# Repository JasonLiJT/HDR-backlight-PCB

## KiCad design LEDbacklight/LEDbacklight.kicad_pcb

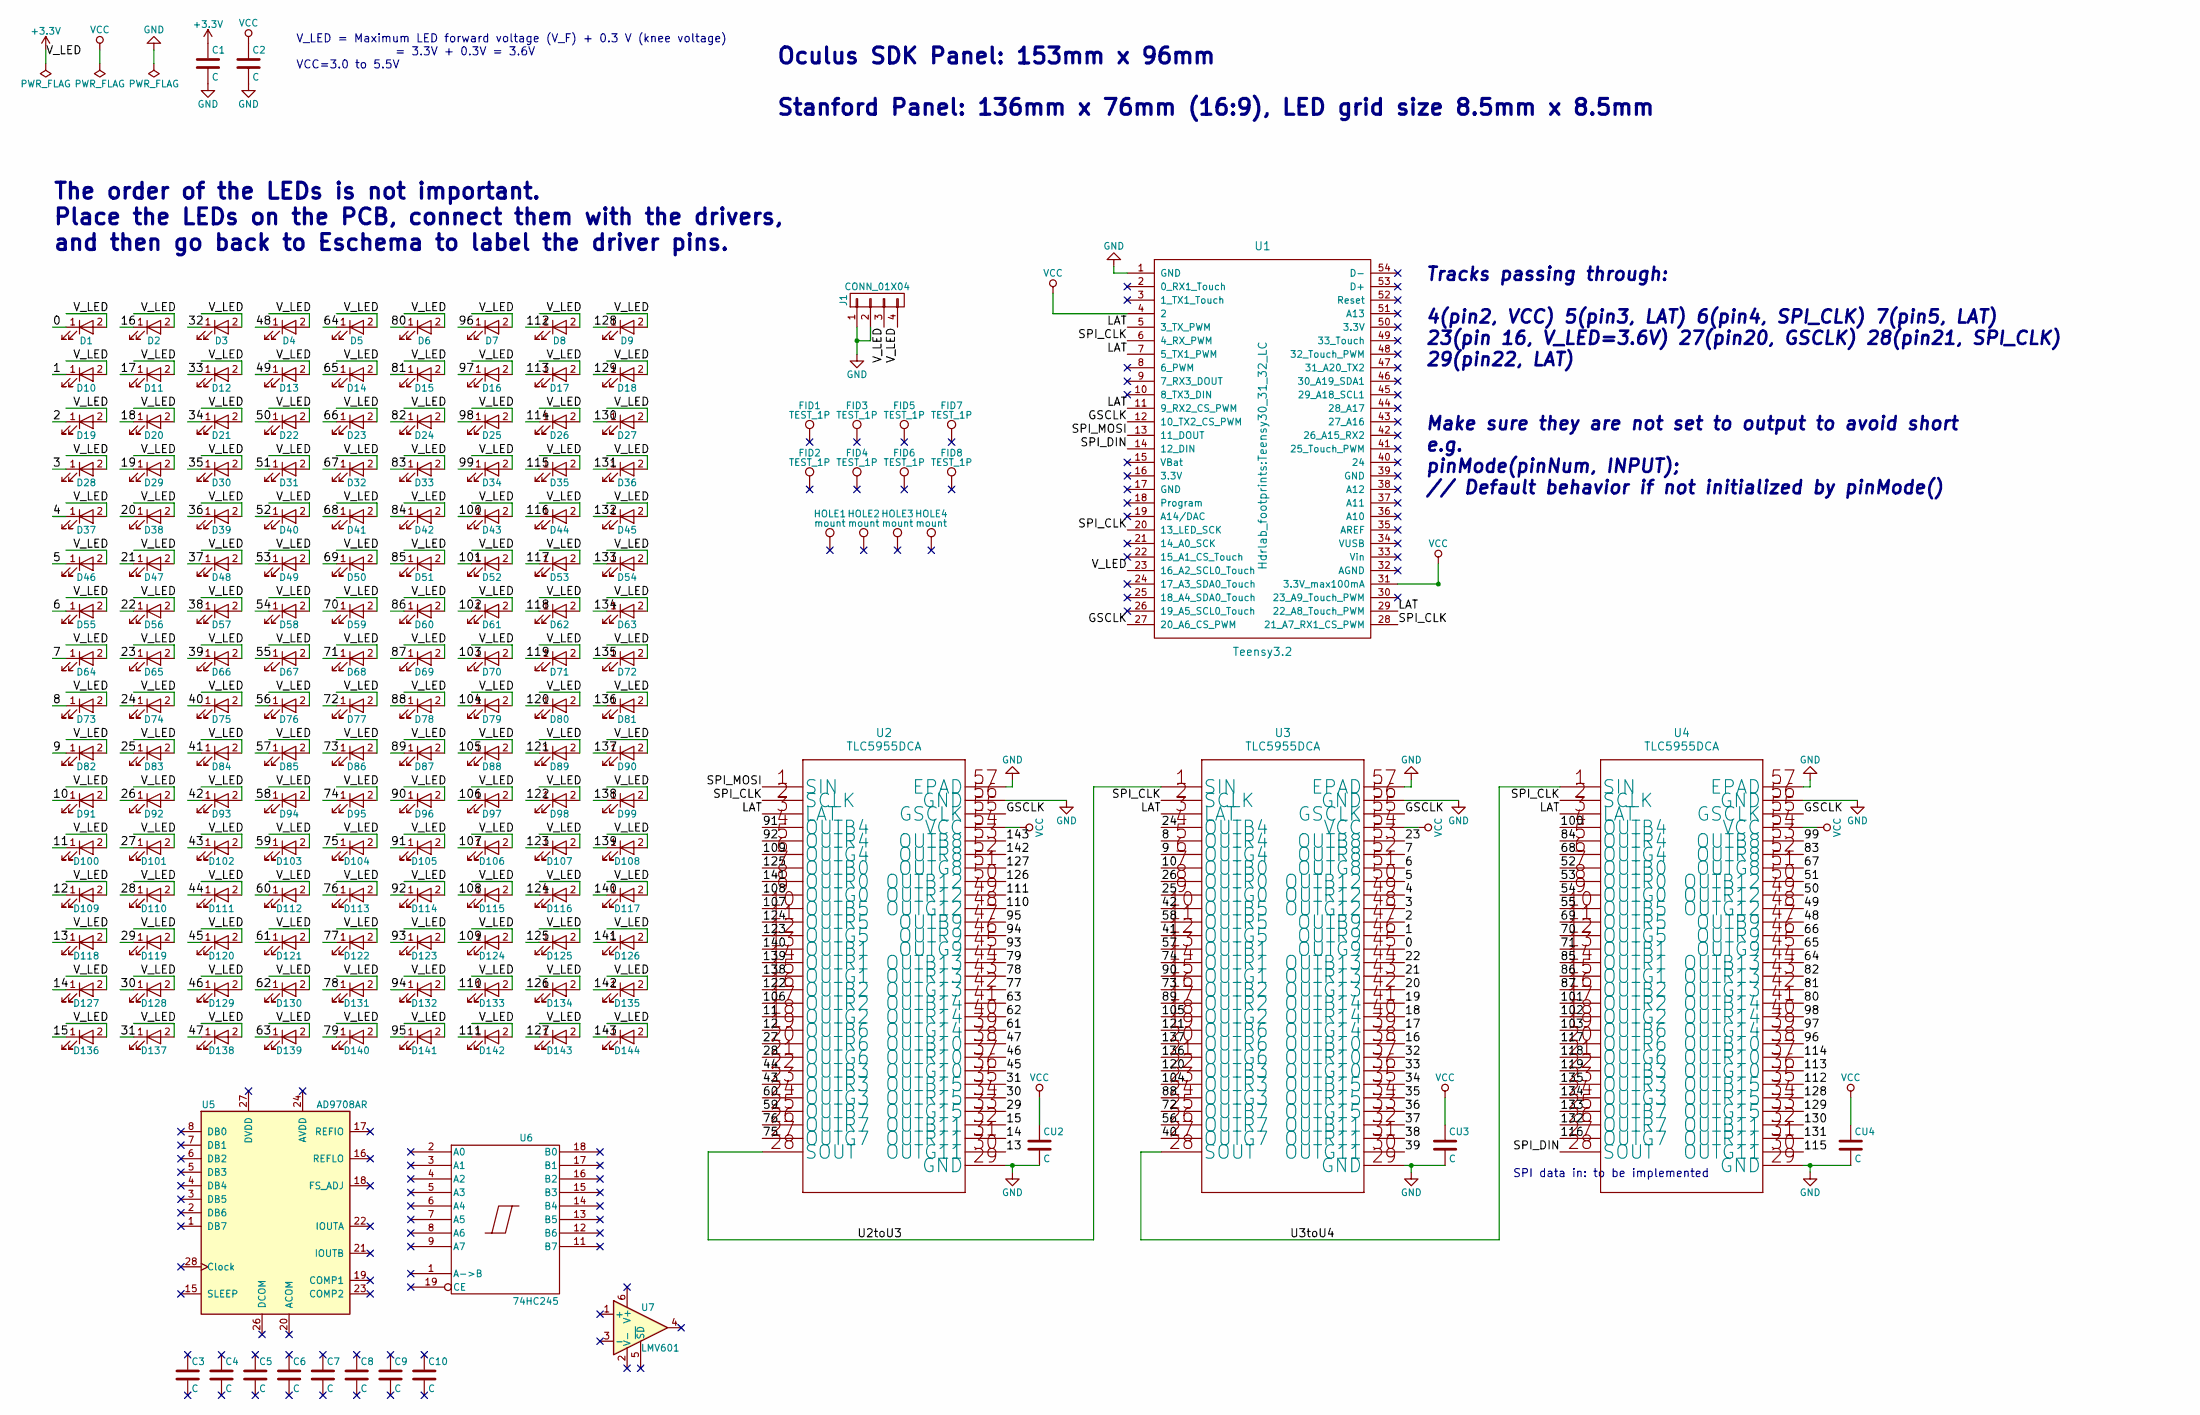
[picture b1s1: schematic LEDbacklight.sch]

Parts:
C1, C2, C3, C4, C5, C6, C7, C8, C9, C10: C; C_0603_HandSoldering
CU2, CU3, CU4: C; C_0603_HandSoldering
D1, D2, D3, D4, D5, D6, D7, D8, D9, D10, D11, D12, D13, D14, D15, D16, D17, D18, D19, D20, D21, D22, D23, D24, D25, D26, D27, D28, D29, D30, D31, D32, D33, D34, D35, D36, D37, D38, D39, D40, D41, D42, D43, D44, D45, D46, D47, D48, D49, D50, D51, D52, D53, D54, D55, D56, D57, D58, D59, D60, D61, D62, D63, D64, D65, D66, D67, D68, D69, D70, D71, D72, D73, D74, D75, D76, D77, D78, D79, D80, D81, D82, D83, D84, D85, D86, D87, D88, D89, D90, D91, D92, D93, D94, D95, D96, D97, D98, D99, D100, D101, D102, D103, D104, D105, D106, D107, D108, D109, D110, D111, D112, D113, D114, D115, D116, D117, D118, D119, D120, D121, D122, D123, D124, D125, D126, D127, D128, D129, D130, D131, D132, D133, D134, D135, D136, D137, D138, D139, D140, D141, D142, D143, D144: LED; LED_6500K
FID1, FID2, FID3, FID4: TEST_1P; Fiducial_1mm_Dia_2.54mm_Outer_CopperTop
FID5, FID6, FID7, FID8: TEST_1P; Fiducial_1mm_Dia_2.54mm_Outer_CopperBottom
HOLE1, HOLE2, HOLE3, HOLE4: mount; MountingHole_2.7mm_M2.5
J1: CONN_01X04; Molex_KK-6410-04_04x2.54mm_Straight
U1: Teensy3.2; Teensy30_31_32_LC
U2, U3, U4: TLC5955DCA
U5: AD9708AR; ETSSOP-20-1EP_4.4x6.5mm_Pitch0.65mm
U6: 74HC245; SSOP-20
U7: LMV601; SOT-23-6_Handsoldering

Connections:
+3V3: C1.1, D1.2 (A), D2.2 (A), D3.2 (A), D4.2 (A), D5.2 (A), D6.2 (A), D7.2 (A), D8.2 (A), D9.2 (A), D10.2 (A), D11.2 (A), D12.2 (A), D13.2 (A), D14.2 (A), D15.2 (A), D16.2 (A), D17.2 (A), D18.2 (A), D19.2 (A), D20.2 (A), D21.2 (A), D22.2 (A), D23.2 (A), D24.2 (A), D25.2 (A), D26.2 (A), D27.2 (A), D28.2 (A), D29.2 (A), D30.2 (A), D31.2 (A), D32.2 (A), D33.2 (A), D34.2 (A), D35.2 (A), D36.2 (A), D37.2 (A), D38.2 (A), D39.2 (A), D40.2 (A), D41.2 (A), D42.2 (A), D43.2 (A), D44.2 (A), D45.2 (A), D46.2 (A), D47.2 (A), D48.2 (A), D49.2 (A), D50.2 (A), D51.2 (A), D52.2 (A), D53.2 (A), D54.2 (A), D55.2 (A), D56.2 (A), D57.2 (A), D58.2 (A), D59.2 (A), D60.2 (A), D61.2 (A), D62.2 (A), D63.2 (A), D64.2 (A), D65.2 (A), D66.2 (A), D67.2 (A), D68.2 (A), D69.2 (A), D70.2 (A), D71.2 (A), D72.2 (A), D73.2 (A), D74.2 (A), D75.2 (A), D76.2 (A), D77.2 (A), D78.2 (A), D79.2 (A), D80.2 (A), D81.2 (A), D82.2 (A), D83.2 (A), D84.2 (A), D85.2 (A), D86.2 (A), D87.2 (A), D88.2 (A), D89.2 (A), D90.2 (A), D91.2 (A), D92.2 (A), D93.2 (A), D94.2 (A), D95.2 (A), D96.2 (A), D97.2 (A), D98.2 (A), D99.2 (A), D100.2 (A), D101.2 (A), D102.2 (A), D103.2 (A), D104.2 (A), D105.2 (A), D106.2 (A), D107.2 (A), D108.2 (A), D109.2 (A), D110.2 (A), D111.2 (A), D112.2 (A), D113.2 (A), D114.2 (A), D115.2 (A), D116.2 (A), D117.2 (A), D118.2 (A), D119.2 (A), D120.2 (A), D121.2 (A), D122.2 (A), D123.2 (A), D124.2 (A), D125.2 (A), D126.2 (A), D127.2 (A), D128.2 (A), D129.2 (A), D130.2 (A), D131.2 (A), D132.2 (A), D133.2 (A), D134.2 (A), D135.2 (A), D136.2 (A), D137.2 (A), D138.2 (A), D139.2 (A), D140.2 (A), D141.2 (A), D142.2 (A), D143.2 (A), D144.2 (A), J1.3, J1.4, U1.23 (16_A2_SCL0_Touch)
/0: D1.1 (K), U3.45 (OUTG9)
/1: D10.1 (K), U3.46 (OUTR9)
/2: D19.1 (K), U3.47 (OUTB9)
/3: D28.1 (K), U3.48 (OUTG12)
/4: D37.1 (K), U3.49 (OUTR12)
/5: D46.1 (K), U3.50 (OUTB12)
/6: D55.1 (K), U3.51 (OUTG8)
/7: D64.1 (K), U3.52 (OUTR8)
/8: D73.1 (K), U3.5 (OUTR4)
/9: D82.1 (K), U3.6 (OUTG4)
/10: D91.1 (K), U3.7 (OUTB0)
/11: D100.1 (K), U2.18 (OUTG2)
/12: D109.1 (K), U2.19 (OUTB6)
/13: D118.1 (K), U2.30 (OUTG11)
/14: D127.1 (K), U2.31 (OUTR11)
/15: D136.1 (K), U2.32 (OUTB11)
/16: D2.1 (K), U3.38 (OUTB10)
/17: D11.1 (K), U3.39 (OUTG14)
/18: D20.1 (K), U3.40 (OUTR14)
/19: D29.1 (K), U3.41 (OUTB14)
/20: D38.1 (K), U3.42 (OUTG13)
/21: D47.1 (K), U3.43 (OUTR13)
/22: D56.1 (K), U3.44 (OUTB13)
/23: D65.1 (K), U3.53 (OUTB8)
/24: D74.1 (K), U3.4 (OUTB4)
/25: D83.1 (K), U3.9 (OUTG0)
/26: D92.1 (K), U3.8 (OUTR0)
/27: D101.1 (K), U2.20 (OUTR6)
/28: D110.1 (K), U2.21 (OUTG6)
/29: D119.1 (K), U2.33 (OUTG15)
/30: D128.1 (K), U2.34 (OUTR15)
/31: D137.1 (K), U2.35 (OUTB15)
/32: D3.1 (K), U3.37 (OUTR10)
/33: D12.1 (K), U3.36 (OUTG10)
/34: D21.1 (K), U3.35 (OUTB15)
/35: D30.1 (K), U3.34 (OUTR15)
/36: D39.1 (K), U3.33 (OUTG15)
/37: D48.1 (K), U3.32 (OUTB11)
/38: D57.1 (K), U3.31 (OUTR11)
/39: D66.1 (K), U3.30 (OUTG11)
/40: D75.1 (K), U3.27 (OUTG7)
/41: D84.1 (K), U3.12 (OUTG5)
/42: D93.1 (K), U3.10 (OUTB5)
/43: D102.1 (K), U2.23 (OUTR3)
/44: D111.1 (K), U2.22 (OUTB3)
/45: D120.1 (K), U2.36 (OUTG10)
/46: D129.1 (K), U2.37 (OUTR10)
/47: D138.1 (K), U2.38 (OUTB10)
/48: D4.1 (K), U4.47 (OUTB9)
/49: D13.1 (K), U4.48 (OUTG12)
/50: D22.1 (K), U4.49 (OUTR12)
/51: D31.1 (K), U4.50 (OUTB12)
/52: D40.1 (K), U4.7 (OUTB0)
/53: D49.1 (K), U4.8 (OUTR0)
/54: D58.1 (K), U4.9 (OUTG0)
/55: D67.1 (K), U4.10 (OUTB5)
/56: D76.1 (K), U3.26 (OUTR7)
/57: D85.1 (K), U3.13 (OUTB1)
/58: D94.1 (K), U3.11 (OUTR5)
/59: D103.1 (K), U2.25 (OUTB7)
/60: D112.1 (K), U2.24 (OUTG3)
/61: D121.1 (K), U2.39 (OUTG14)
/62: D130.1 (K), U2.40 (OUTR14)
/63: D139.1 (K), U2.41 (OUTB14)
/64: D5.1 (K), U4.44 (OUTB13)
/65: D14.1 (K), U4.45 (OUTG9)
/66: D23.1 (K), U4.46 (OUTR9)
/67: D32.1 (K), U4.51 (OUTG8)
/68: D41.1 (K), U4.6 (OUTG4)
/69: D50.1 (K), U4.11 (OUTR5)
/70: D59.1 (K), U4.12 (OUTG5)
/71: D68.1 (K), U4.13 (OUTB1)
/72: D77.1 (K), U3.25 (OUTB7)
/73: D86.1 (K), U3.16 (OUTB2)
/74: D95.1 (K), U3.14 (OUTR1)
/75: D104.1 (K), U2.27 (OUTG7)
/76: D113.1 (K), U2.26 (OUTR7)
/77: D122.1 (K), U2.42 (OUTG13)
/78: D131.1 (K), U2.43 (OUTR13)
/79: D140.1 (K), U2.44 (OUTB13)
/80: D6.1 (K), U4.41 (OUTB14)
/81: D15.1 (K), U4.42 (OUTG13)
/82: D24.1 (K), U4.43 (OUTR13)
/83: D33.1 (K), U4.52 (OUTR8)
/84: D42.1 (K), U4.5 (OUTR4)
/85: D51.1 (K), U4.14 (OUTR1)
/86: D60.1 (K), U4.15 (OUTG1)
/87: D69.1 (K), U4.16 (OUTB2)
/88: D78.1 (K), U3.24 (OUTG3)
/89: D87.1 (K), U3.17 (OUTR2)
/90: D96.1 (K), U3.15 (OUTG1)
/91: D105.1 (K), U2.4 (OUTB4)
/92: D114.1 (K), U2.5 (OUTR4)
/93: D123.1 (K), U2.45 (OUTG9)
/94: D132.1 (K), U2.46 (OUTR9)
/95: D141.1 (K), U2.47 (OUTB9)
/96: D7.1 (K), U4.38 (OUTB10)
/97: D16.1 (K), U4.39 (OUTG14)
/98: D25.1 (K), U4.40 (OUTR14)
/99: D34.1 (K), U4.53 (OUTB8)
/100: D43.1 (K), U4.4 (OUTB4)
/101: D52.1 (K), U4.17 (OUTR2)
/102: D61.1 (K), U4.18 (OUTG2)
/103: D70.1 (K), U4.19 (OUTB6)
/104: D79.1 (K), U3.23 (OUTR3)
/105: D88.1 (K), U3.18 (OUTG2)
/106: D97.1 (K), U2.17 (OUTR2)
/107: D106.1 (K), U2.10 (OUTB5)
/108: D115.1 (K), U2.9 (OUTG0)
/109: D124.1 (K), U2.6 (OUTG4)
/110: D133.1 (K), U2.48 (OUTG12)
/111: D142.1 (K), U2.49 (OUTR12)
/112: D8.1 (K), U4.35 (OUTB15)
/113: D17.1 (K), U4.36 (OUTG10)
/114: D26.1 (K), U4.37 (OUTR10)
/115: D35.1 (K), U4.30 (OUTG11)
/116: D44.1 (K), U4.27 (OUTG7)
/117: D53.1 (K), U4.20 (OUTR6)
/118: D62.1 (K), U4.21 (OUTG6)
/119: D71.1 (K), U4.22 (OUTB3)
/120: D80.1 (K), U3.22 (OUTB3)
/121: D89.1 (K), U3.19 (OUTB6)
/122: D98.1 (K), U2.16 (OUTB2)
/123: D107.1 (K), U2.12 (OUTG5)
/124: D116.1 (K), U2.11 (OUTR5)
/125: D125.1 (K), U2.7 (OUTB0)
/126: D134.1 (K), U2.50 (OUTB12)
/127: D143.1 (K), U2.51 (OUTG8)
/128: D9.1 (K), U4.34 (OUTR15)
/129: D18.1 (K), U4.33 (OUTG15)
/130: D27.1 (K), U4.32 (OUTB11)
/131: D36.1 (K), U4.31 (OUTR11)
/132: D45.1 (K), U4.26 (OUTR7)
/133: D54.1 (K), U4.25 (OUTB7)
/134: D63.1 (K), U4.24 (OUTG3)
/135: D72.1 (K), U4.23 (OUTR3)
/136: D81.1 (K), U3.21 (OUTG6)
/137: D90.1 (K), U3.20 (OUTR6)
/138: D99.1 (K), U2.15 (OUTG1)
/139: D108.1 (K), U2.14 (OUTR1)
/140: D117.1 (K), U2.13 (OUTB1)
/141: D126.1 (K), U2.8 (OUTR0)
/142: D135.1 (K), U2.52 (OUTR8)
/143: D144.1 (K), U2.53 (OUTB8)
/GSCLK: U1.12 (10_TX2_CS_PWM), U1.27 (20_A6_CS_PWM), U2.55 (GSCLK), U3.55 (GSCLK), U4.55 (GSCLK)
/LAT: U1.5 (3_TX_PWM), U1.7 (5_TX1_PWM), U1.11 (9_RX2_CS_PWM), U1.29 (22_A8_Touch_PWM), U2.3 (LAT), U3.3 (LAT), U4.3 (LAT)
/SPI_CLK: U1.6 (4_RX_PWM), U1.20 (13_LED_SCK), U1.28 (21_A7_RX1_CS_PWM), U2.2 (SCLK), U3.2 (SCLK), U4.2 (SCLK)
/SPI_DIN: U1.14 (12_DIN), U4.28 (SOUT)
/SPI_MOSI: U1.13 (11_DOUT), U2.1 (SIN)
/U2toU3: U2.28 (SOUT), U3.1 (SIN)
/U3toU4: U3.28 (SOUT), U4.1 (SIN)
GND: C1.2, C2.2, CU2.2, CU3.2, CU4.2, J1.1, J1.2, U1.1 (GND), U2.29 (GND), U2.56 (GND), U2.57 (EPAD), U3.29 (GND), U3.56 (GND), U3.57 (EPAD), U4.29 (GND), U4.56 (GND), U4.57 (EPAD), U6.10 (GND)
VCC: C2.1, CU2.1, CU3.1, CU4.1, U1.4 (2), U1.31 (3.3V_max100mA), U2.54 (VCC), U3.54 (VCC), U4.54 (VCC), U6.20 (VCC)

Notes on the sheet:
V_LED = Maximum LED forward voltage (V_F) + 0.3 V (knee voltage) = 3.3V + 0.3V = 3.6V VCC=3.0 to 5.5V
Oculus SDK Panel: 153mm x 96mm Stanford Panel: 136mm x 76mm (16:9), LED grid size 8.5mm x 8.5mm
The order of the LEDs is not important. Place the LEDs on the PCB, connect them with the drivers, and then go back to Eschema to label the driver pins.
SPI data in: to be implemented
Tracks passing through: 4(pin2, VCC) 5(pin3, LAT) 6(pin4, SPI_CLK) 7(pin5, LAT) 23(pin 16, V_LED=3.6V) 27(pin20, GSCLK) 28(pin21, SPI_CLK) 29(pin22, LAT) Make sure they are not set to output to avoid short e.g. pinMode(pinNum, INPUT); // Default behavior if not initialized by pinMode()

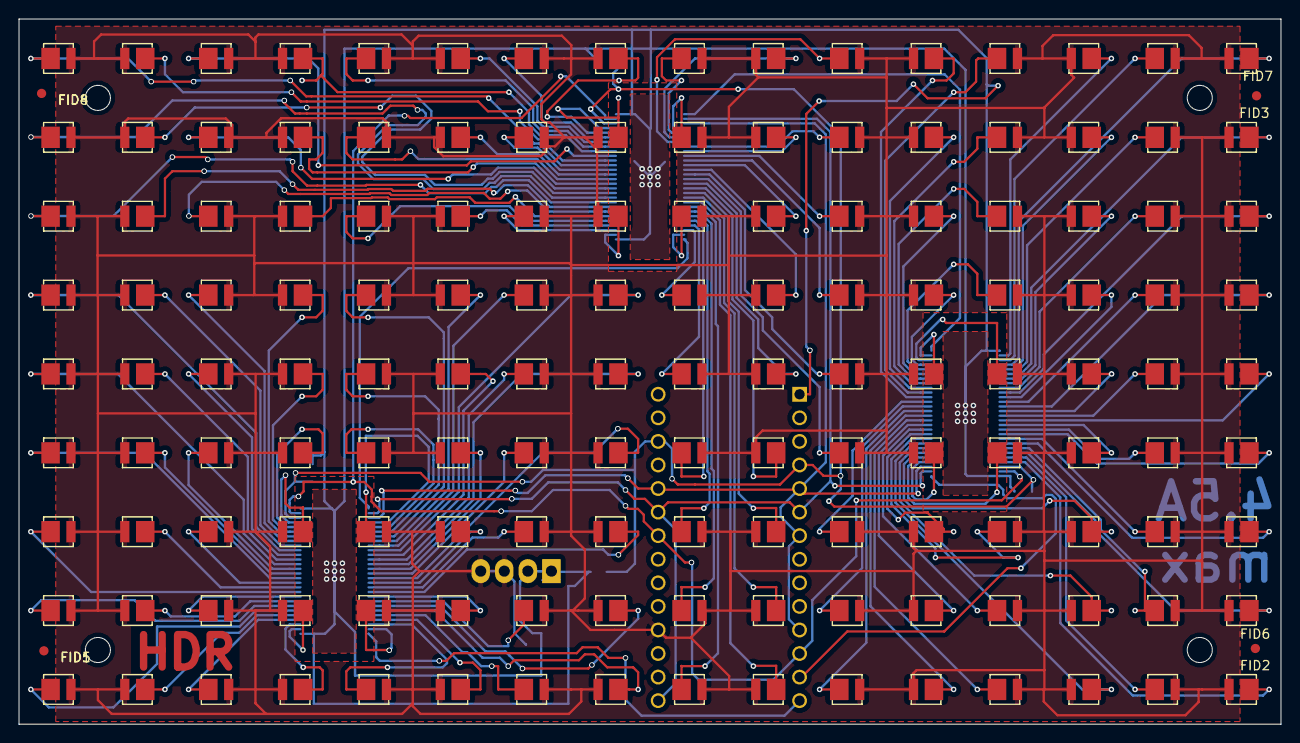
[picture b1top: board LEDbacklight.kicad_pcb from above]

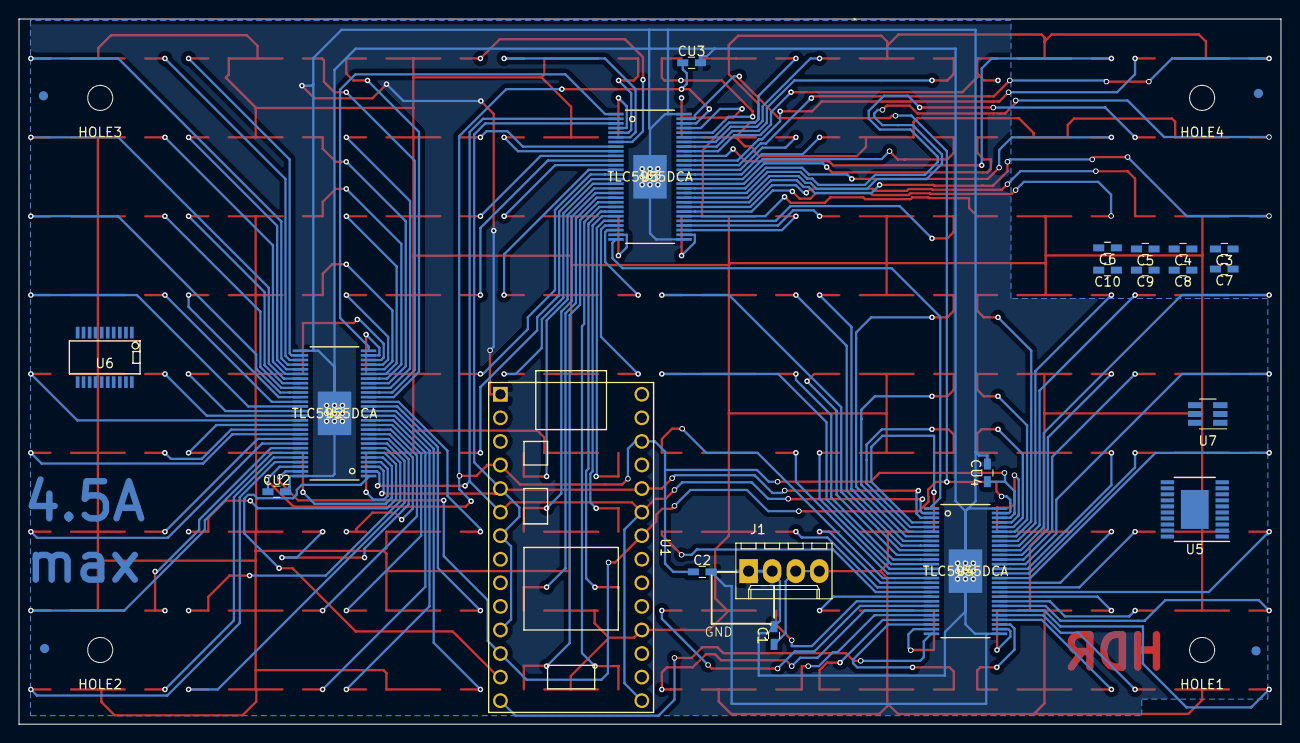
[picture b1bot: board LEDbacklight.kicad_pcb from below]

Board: 2 copper layers, 136.0 x 76.0 mm, 177 parts (25 on the bottom side), 154 nets.

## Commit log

2017-08-10 LED array drawn
2017-08-10 footprint downloaded
2017-08-11 driver footprints downloaded
2017-08-14 LED footprint draft
2017-08-15 Data sheet circuit
2017-08-15 ARM microcontroller, docs and footprints added
2017-08-16 PCB draft created
2017-08-17 teensy lib for kicad added
2017-08-18 LED matrix with power placed
2017-08-18 Teensy footprint fixed
2017-08-23 layout hydrogen
2017-08-24 Vias & power tracks added
2017-08-24 Vias and power update 1
2017-08-24 vias and power update 2
2017-08-24 pins updated
2017-08-25 All GND grounded
2017-08-25 Tracks update
2017-08-25 LED tracks fanpishui
2017-08-25 LED tracks done, clearance 0.2 track width 2.5 Via Dia 0.6
2017-08-25 add TODO in PCBnew
2017-08-29 tracks cleared
2017-08-29 Rearranged layout
2017-08-29 footprints clearance and SMD updated
2017-08-29 ultimate freeroute configuration
2017-08-29 ground all routed
2017-08-30 hole gaps kept out for auto-routing
2017-08-30 Keepout area cut so that DRC debug works
2017-08-30 Duplicate connection debugged
2017-08-30 LED arrangement optimized
2017-08-30 Auxiliary origin set
2017-08-30 3 unconnected with 2 easy fixes
2017-08-30 Gerber plot configured
2017-08-30 Footprints config for Gerber
2017-08-30 Fiducials and decoupling capacitors added
2017-08-31 before routing
2017-08-31 DRC passed
2017-08-31 Power tracks widened
2017-08-31 Finalized
2017-08-31 TRULY Finalized

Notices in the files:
parts and their libraries:
Copyright 2016 Accelerated Designs. All rights reserved.
